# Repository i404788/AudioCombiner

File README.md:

# Audio Combiner/Amp

> Check out the blog post at https://blog.devdroplets.com/stereo-audio-combiner/

This repository contains the KiCAD files for an analog audio combiner (2-stereo signals) with an Class B Amp.
The board is rated up to 18V, but tested on 12V. Excepted power usage at 12V is 3W, though this will depend on your input.
The board is `64.2x34.3x14mm` (smaller than a creditcard in width/height `85.6x54mm`)

The entire board should cost about 13$ (in materials) when produced as one-off; and 7.5$/board when producing in batches of 5; higher quantities should be even cheaper.

# Custom Components/Footprints
This repository contains a custom Lib for KiCAD which includes the TDA1517 (SIP-9) component, which can be reused.
The TDA1517 is a cheap Class B stereo amp, available for 0.17$.

# Screenshots

# License
This hardware is licensed under 
[Creative Commons Attribution 4.0 International License.](https://creativecommons.org/licenses/by/4.0/)

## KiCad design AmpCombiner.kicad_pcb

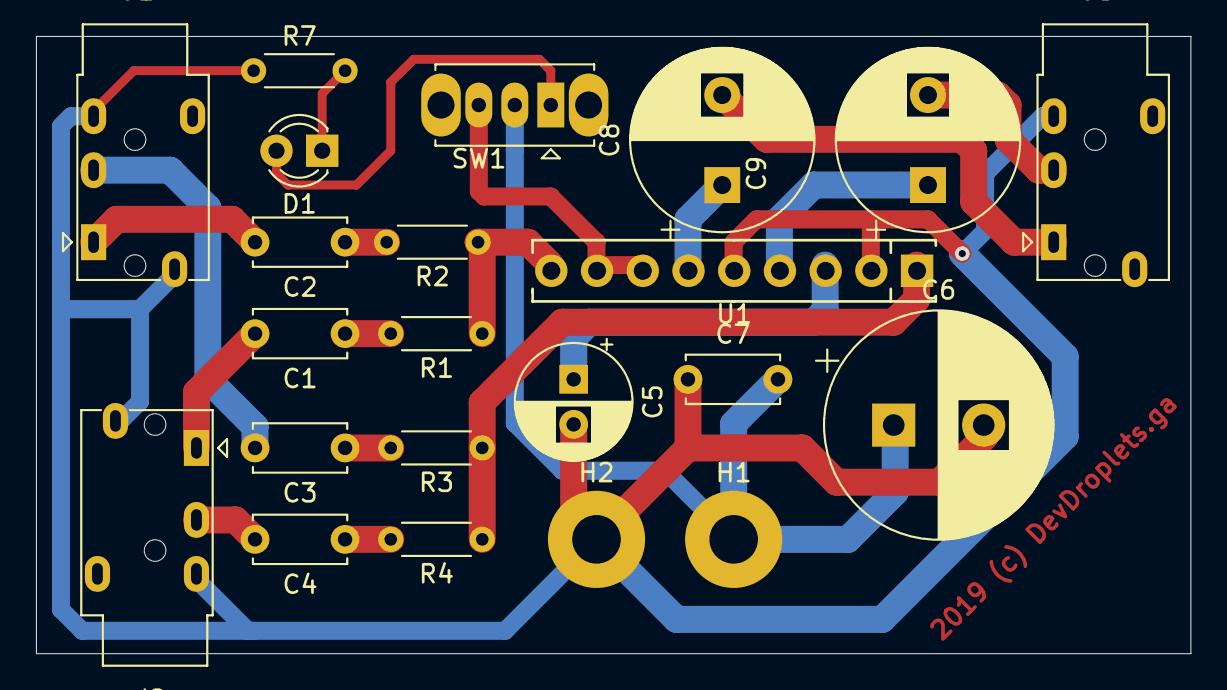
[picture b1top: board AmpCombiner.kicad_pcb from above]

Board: 2 copper layers, 64.1 x 34.3 mm, 22 parts (0 on the bottom side), 20 nets.

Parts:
C1, C2, C3, C4: 220u 25v; C_Disc_D5.0mm_W2.5mm_P5.00mm
C5: 100u 25v; CP_Radial_D6.3mm_P2.50mm
C6: 2200u 25v; CP_Radial_D12.5mm_P5.00mm
C7: 100n 25v; C_Disc_D5.0mm_W2.5mm_P5.00mm
C8, C9: 1000u 25v; CP_Radial_D10.0mm_P5.00mm
D1: LED; LED_D3.0mm
H1: Pad+; MountingHole_2.7mm_Pad
H2: Pad-; MountingHole_2.7mm_Pad
J1, J2, J3: AudioJack4; Jack_3.5mm_PJ320E_Horizontal
R1, R2, R3, R4: 10k; R_Axial_DIN0204_L3.6mm_D1.6mm_P5.08mm_Horizontal
R7: 1.5k; R_Axial_DIN0204_L3.6mm_D1.6mm_P5.08mm_Horizontal
SW1: SW_SPDT; SW_Slide_1P2T_CK_OS102011MS2Q
U1: TDA1517; SIP9_Housing

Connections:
+9V: C6.1, C7.2, H1.1, SW1.2
GND: C5.2, C6.2, C7.1, H2.1, J1.R2, J1.S, J2.R2, J2.S, J3.R2, R7.1, U1.2, U1.5
unnamed: C1.1, R1.2
unnamed: C1.2, J2.T
unnamed: C2.1, R2.2
unnamed: C2.2, J1.T
unnamed: C3.1, R3.2
unnamed: C3.2, J1.R1
unnamed: C4.1, R4.2
unnamed: C4.2, J2.R1
unnamed: C5.1, U1.3
unnamed: C8.1, U1.6
unnamed: C8.2, J3.T
unnamed: C9.1, U1.4
unnamed: C9.2, J3.R1
unnamed: D1.1, R7.2
unnamed: D1.2, SW1.1
unnamed: R1.1, R2.1, U1.9
unnamed: R3.1, R4.1, U1.1
unnamed: SW1.3, U1.7, U1.8

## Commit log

2019-10-21 Add board, BOM, README
2019-10-21 Update docs, standard footprint
2019-10-21 Better link
